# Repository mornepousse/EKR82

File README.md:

# EKR82 Keyboard

Work in Progress...

EN:

I took the Lily58 and added my personal touch by including a column and row layout for ease of use. I added function keys on top for more efficient use of special functions and an extra macro column for even further customization to my liking. And to top it all off, I added a thumb button for easy access to an important function. In short, the EKR82 is a custom keyboard that I created to meet all of my needs

FR:

J'ai pris le Lily58 et j'ai ajouté ma touche personnelle en y incluant une disposition en colonnes et en rangées pour une utilisation facile. J'ai ajouté des touches de fonction en haut pour une utilisation plus efficace des fonctions spéciales et une colonne de macros pour une personnalisation encore plus poussée a mon goût. Et pour couronner le tout, j'ai ajouté une touche pour le pouce pour un accès facile à une fonction importante. Bref, le EKR82 est un clavier sur mesure que j'ai créé pour répondre à tous mes besoins.

lily58 forki

by mornepousse

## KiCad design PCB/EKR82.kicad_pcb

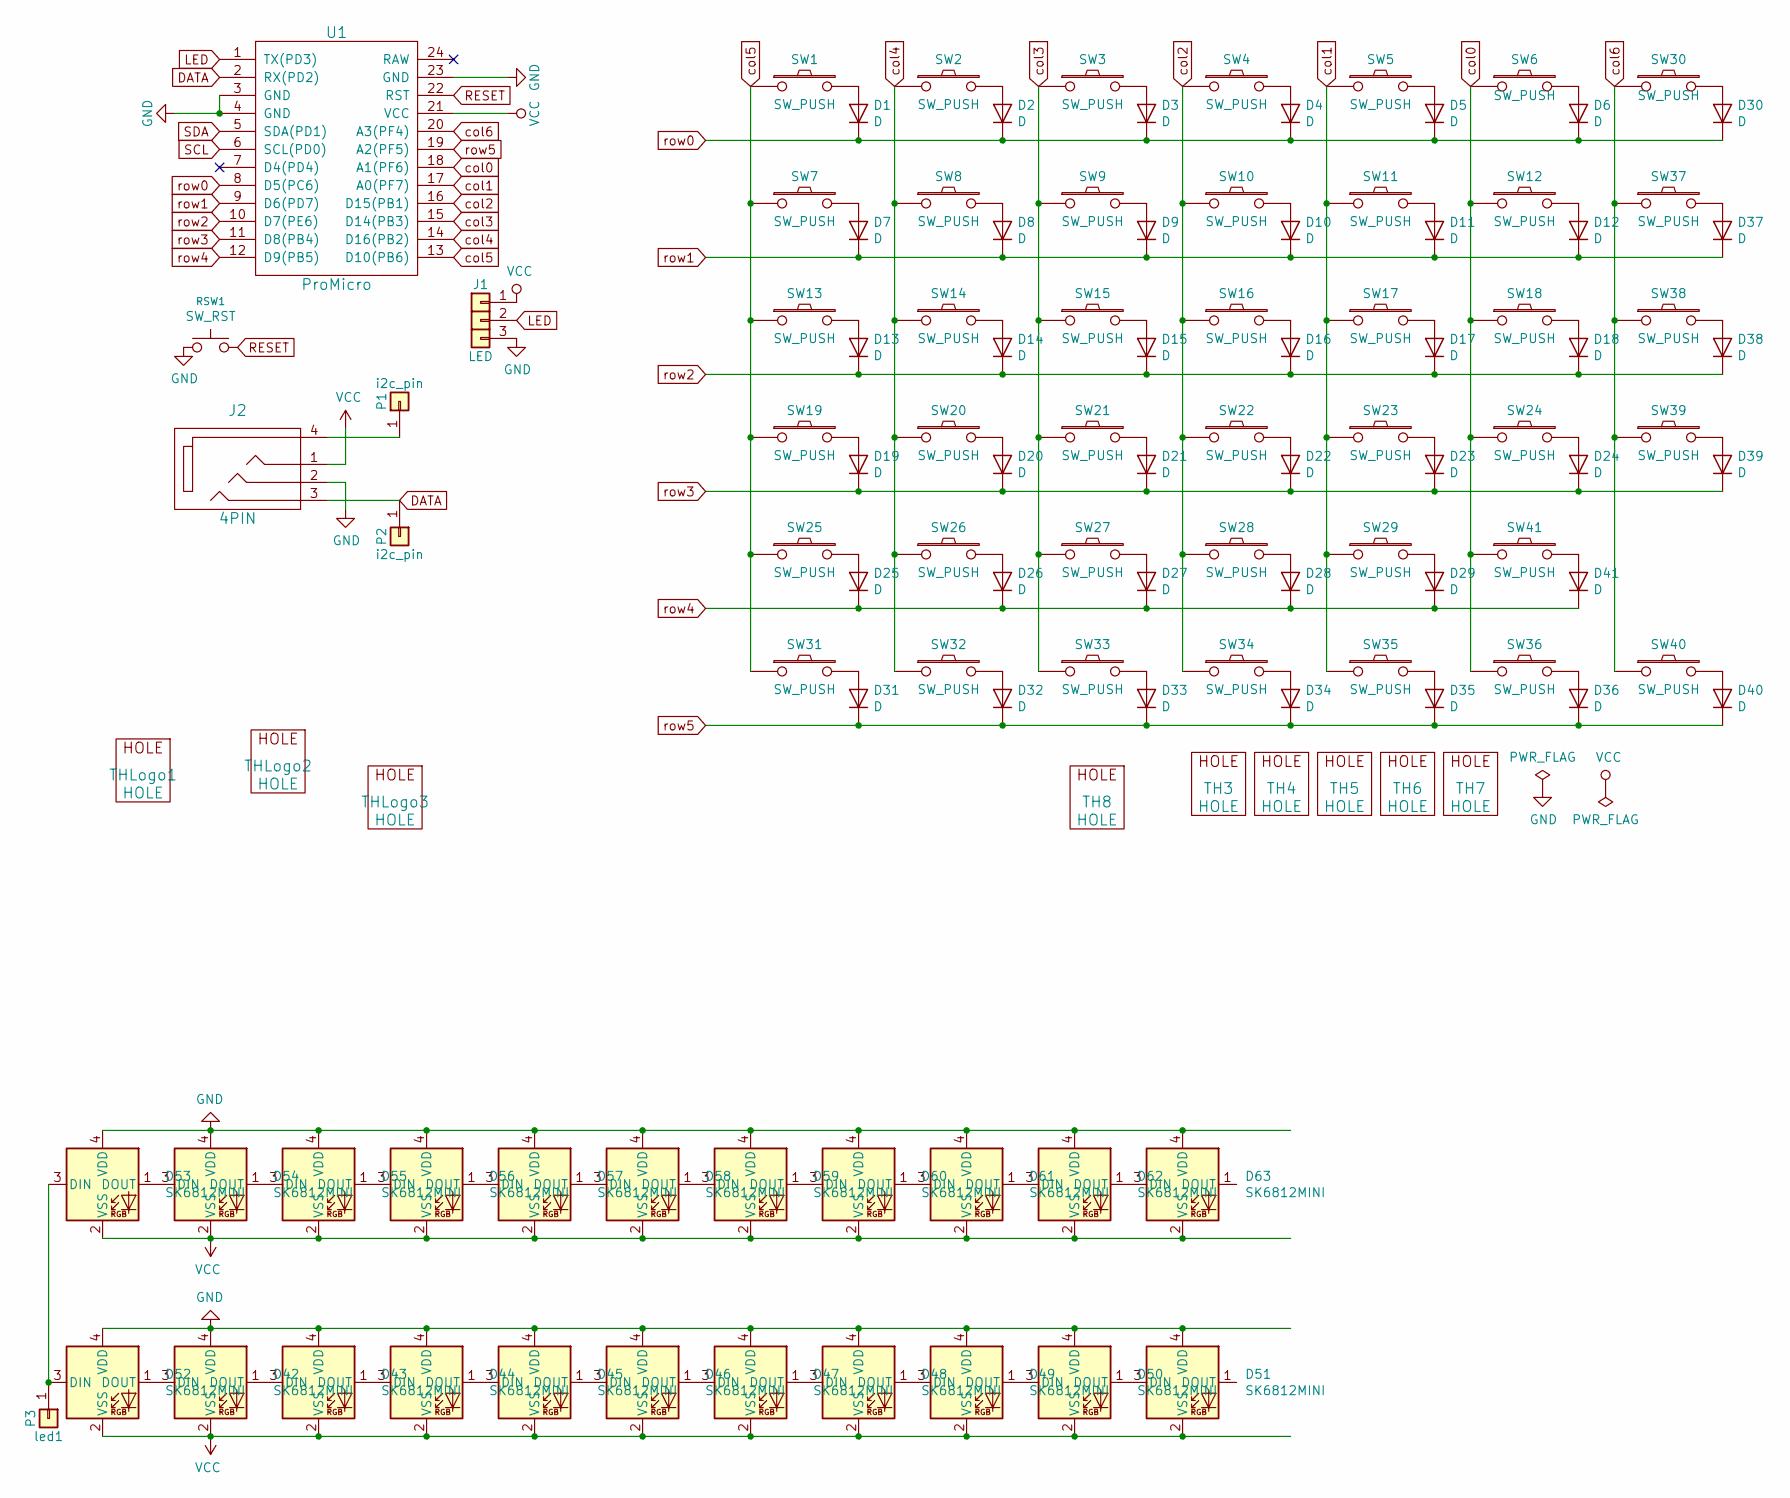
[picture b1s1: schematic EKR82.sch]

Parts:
D1, D2, D3, D4, D5, D6, D7, D8, D9, D10, D11, D12, D13, D14, D15, D16, D17, D18, D19, D20, D21, D22, D23, D24, D25, D26, D27, D28, D29, D30, D31, D32, D33, D34, D35, D36, D37, D38, D39, D40, D41: D; Diode_SOD123
D42, D43, D44, D45, D46, D47, D48, D49, D50, D51, D52, D53, D54, D55, D56, D57, D58, D59, D60, D61, D62, D63: SK6812MINI; LED_SK6812MINI_PLCC4_3.5x3.5mm_P1.75mm
J1: LED
J2: 4PIN; MJ-4PP-9
P1, P2: i2c_pin; 1pin_conn
P3: led1; PinHeader_1x01_P1.27mm_Vertical
RSW1: SW_RST; TACT_SWITCH_TVBP06
SW1, SW2, SW3, SW4, SW5, SW6, SW7, SW8, SW9, SW10, SW11, SW12, SW13, SW14, SW15, SW16, SW17, SW18, SW19, SW20, SW21, SW22, SW23, SW24, SW25, SW26, SW27, SW28, SW29, SW30, SW31, SW32, SW33, SW34, SW35, SW36, SW37, SW38, SW39, SW40, SW41: SW_PUSH; CherryMX_KailhLowProfile_Hotswap_edge-2
TH3, TH4, TH5, TH6, TH7, TH8: HOLE; HOLE_M2_TH
THLogo1: HOLE; EKR82-2
THLogo2, THLogo3: HOLE; OSHW-Symbol_8.9x8mm_SilkScreen
U1: ProMicro; ProMicro_rev

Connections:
DATA: J2.3, P2.1, U1.2 (RX(PD2))
GND: D42.4 (VDD), D43.4 (VDD), D44.4 (VDD), D45.4 (VDD), D46.4 (VDD), D47.4 (VDD), D48.4 (VDD), D49.4 (VDD), D50.4 (VDD), D51.4 (VDD), D52.4 (VDD), D53.4 (VDD), D54.4 (VDD), D55.4 (VDD), D56.4 (VDD), D57.4 (VDD), D58.4 (VDD), D59.4 (VDD), D60.4 (VDD), D61.4 (VDD), D62.4 (VDD), D63.4 (VDD), J1.3, J2.2, RSW1.1, U1.3 (GND), U1.4 (GND), U1.23 (GND)
LED: J1.2, U1.1 (TX(PD3))
unnamed: D1.2 (A), SW1.2
unnamed: D2.2 (A), SW2.2
unnamed: D3.2 (A), SW3.2
unnamed: D4.2 (A), SW4.2
unnamed: D5.2 (A), SW5.2
unnamed: D6.2 (A), SW6.2
unnamed: D7.2 (A), SW7.2
unnamed: D8.2 (A), SW8.2
unnamed: D9.2 (A), SW9.2
unnamed: D10.2 (A), SW10.2
unnamed: D11.2 (A), SW11.2
unnamed: D12.2 (A), SW12.2
unnamed: D13.2 (A), SW13.2
unnamed: D14.2 (A), SW14.2
unnamed: D15.2 (A), SW15.2
unnamed: D16.2 (A), SW16.2
unnamed: D17.2 (A), SW17.2
unnamed: D18.2 (A), SW18.2
unnamed: D19.2 (A), SW19.2
unnamed: D20.2 (A), SW20.2
unnamed: D21.2 (A), SW21.2
unnamed: D22.2 (A), SW22.2
unnamed: D23.2 (A), SW23.2
unnamed: D24.2 (A), SW24.2
unnamed: D25.2 (A), SW25.2
unnamed: D26.2 (A), SW26.2
unnamed: D27.2 (A), SW27.2
unnamed: D28.2 (A), SW28.2
unnamed: D29.2 (A), SW29.2
unnamed: D30.2 (A), SW30.2
unnamed: D31.2 (A), SW31.2
unnamed: D32.2 (A), SW32.2
unnamed: D33.2 (A), SW33.2
unnamed: D34.2 (A), SW34.2
unnamed: D35.2 (A), SW35.2
unnamed: D36.2 (A), SW36.2
unnamed: D37.2 (A), SW37.2
unnamed: D38.2 (A), SW38.2
unnamed: D39.2 (A), SW39.2
unnamed: D40.2 (A), SW40.2
unnamed: D41.2 (A), SW41.2
unnamed: D42.1 (DOUT), D43.3 (DIN)
unnamed: D42.3 (DIN), D52.1 (DOUT)
unnamed: D43.1 (DOUT), D44.3 (DIN)
unnamed: D44.1 (DOUT), D45.3 (DIN)
unnamed: D45.1 (DOUT), D46.3 (DIN)
unnamed: D46.1 (DOUT), D47.3 (DIN)
unnamed: D47.1 (DOUT), D48.3 (DIN)
unnamed: D48.1 (DOUT), D49.3 (DIN)
unnamed: D49.1 (DOUT), D50.3 (DIN)
unnamed: D50.1 (DOUT), D51.3 (DIN)
unnamed 55: D52.3 (DIN), D53.3 (DIN), P3.1; also elsewhere on the board
unnamed: D53.1 (DOUT), D54.3 (DIN)
unnamed: D54.1 (DOUT), D55.3 (DIN)
unnamed: D55.1 (DOUT), D56.3 (DIN)
unnamed: D56.1 (DOUT), D57.3 (DIN)
unnamed: D57.1 (DOUT), D58.3 (DIN)
unnamed: D58.1 (DOUT), D59.3 (DIN)
unnamed: D59.1 (DOUT), D60.3 (DIN)
unnamed: D60.1 (DOUT), D61.3 (DIN)
unnamed: D61.1 (DOUT), D62.3 (DIN)
unnamed: D62.1 (DOUT), D63.3 (DIN)
unnamed: J2.4, P1.1
RESET: RSW1.2, U1.22 (RST)
SCL: U1.6 (SCL(PD0))
SDA: U1.5 (SDA(PD1))
VCC: D42.2 (VSS), D43.2 (VSS), D44.2 (VSS), D45.2 (VSS), D46.2 (VSS), D47.2 (VSS), D48.2 (VSS), D49.2 (VSS), D50.2 (VSS), D51.2 (VSS), D52.2 (VSS), D53.2 (VSS), D54.2 (VSS), D55.2 (VSS), D56.2 (VSS), D57.2 (VSS), D58.2 (VSS), D59.2 (VSS), D60.2 (VSS), D61.2 (VSS), D62.2 (VSS), D63.2 (VSS), J1.1, J2.1, U1.21 (VCC)
col0: SW6.1, SW12.1, SW18.1, SW24.1, SW36.1, SW41.1, U1.18 (A1(PF6))
col1: SW5.1, SW11.1, SW17.1, SW23.1, SW29.1, SW35.1, U1.17 (A0(PF7))
col2: SW4.1, SW10.1, SW16.1, SW22.1, SW28.1, SW34.1, U1.16 (D15(PB1))
col3: SW3.1, SW9.1, SW15.1, SW21.1, SW27.1, SW33.1, U1.15 (D14(PB3))
col4: SW2.1, SW8.1, SW14.1, SW20.1, SW26.1, SW32.1, U1.14 (D16(PB2))
col5: SW1.1, SW7.1, SW13.1, SW19.1, SW25.1, SW31.1, U1.13 (D10(PB6))
col6: SW30.1, SW37.1, SW38.1, SW39.1, SW40.1, U1.20 (A3(PF4))
row0: D1.1 (K), D2.1 (K), D3.1 (K), D4.1 (K), D5.1 (K), D6.1 (K), D30.1 (K), U1.8 (D5(PC6))
row1: D7.1 (K), D8.1 (K), D9.1 (K), D10.1 (K), D11.1 (K), D12.1 (K), D37.1 (K), U1.9 (D6(PD7))
row2: D13.1 (K), D14.1 (K), D15.1 (K), D16.1 (K), D17.1 (K), D18.1 (K), D38.1 (K), U1.10 (D7(PE6))
row3: D19.1 (K), D20.1 (K), D21.1 (K), D22.1 (K), D23.1 (K), D24.1 (K), D39.1 (K), U1.11 (D8(PB4))
row4: D25.1 (K), D26.1 (K), D27.1 (K), D28.1 (K), D29.1 (K), D41.1 (K), U1.12 (D9(PB5))
row5: D31.1 (K), D32.1 (K), D33.1 (K), D34.1 (K), D35.1 (K), D36.1 (K), D40.1 (K), U1.19 (A2(PF5))

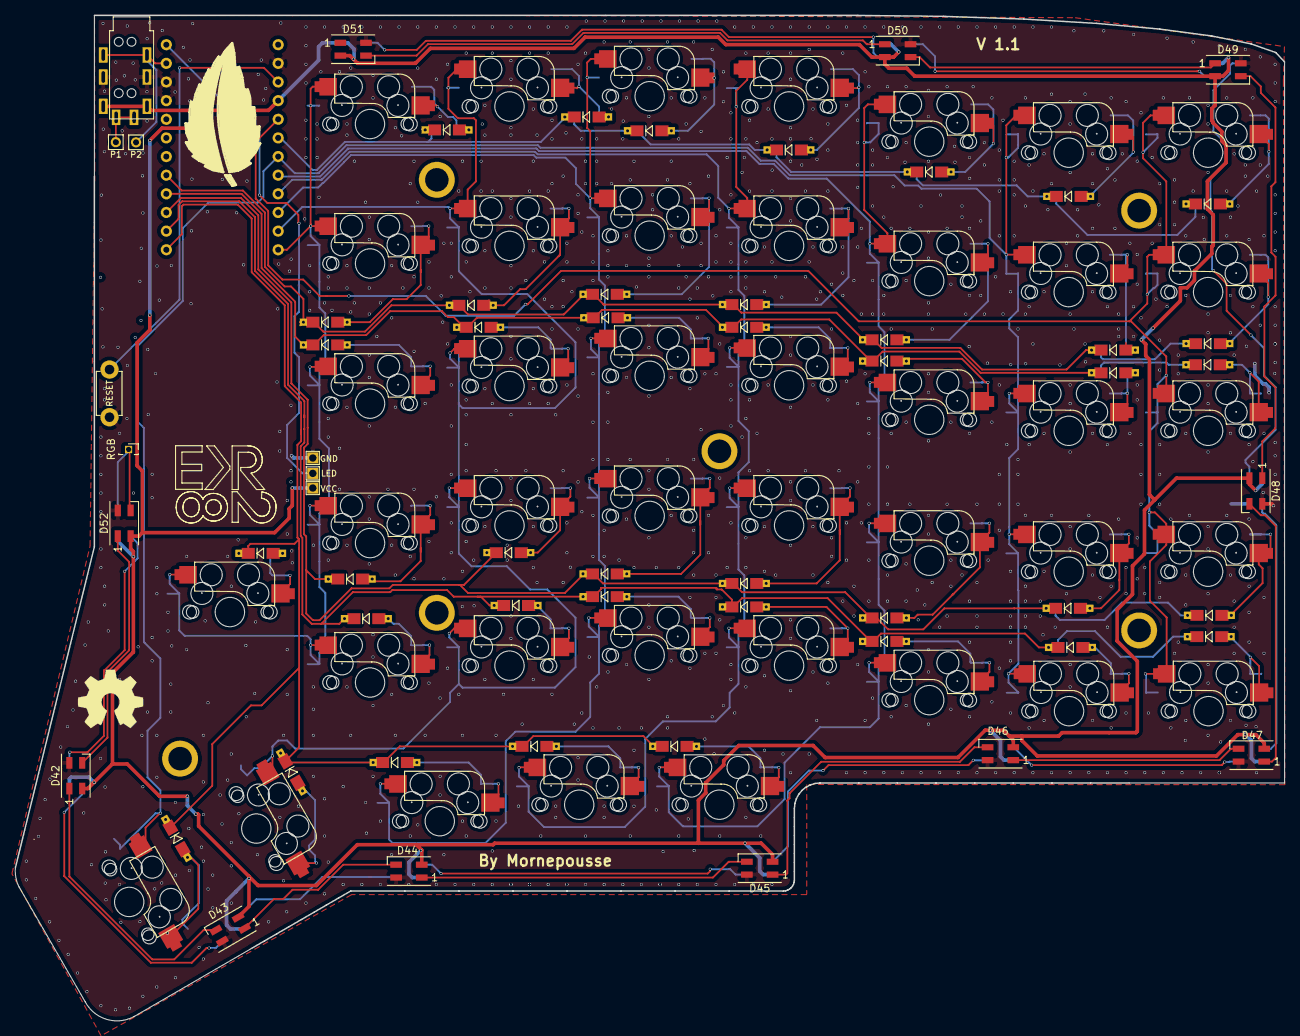
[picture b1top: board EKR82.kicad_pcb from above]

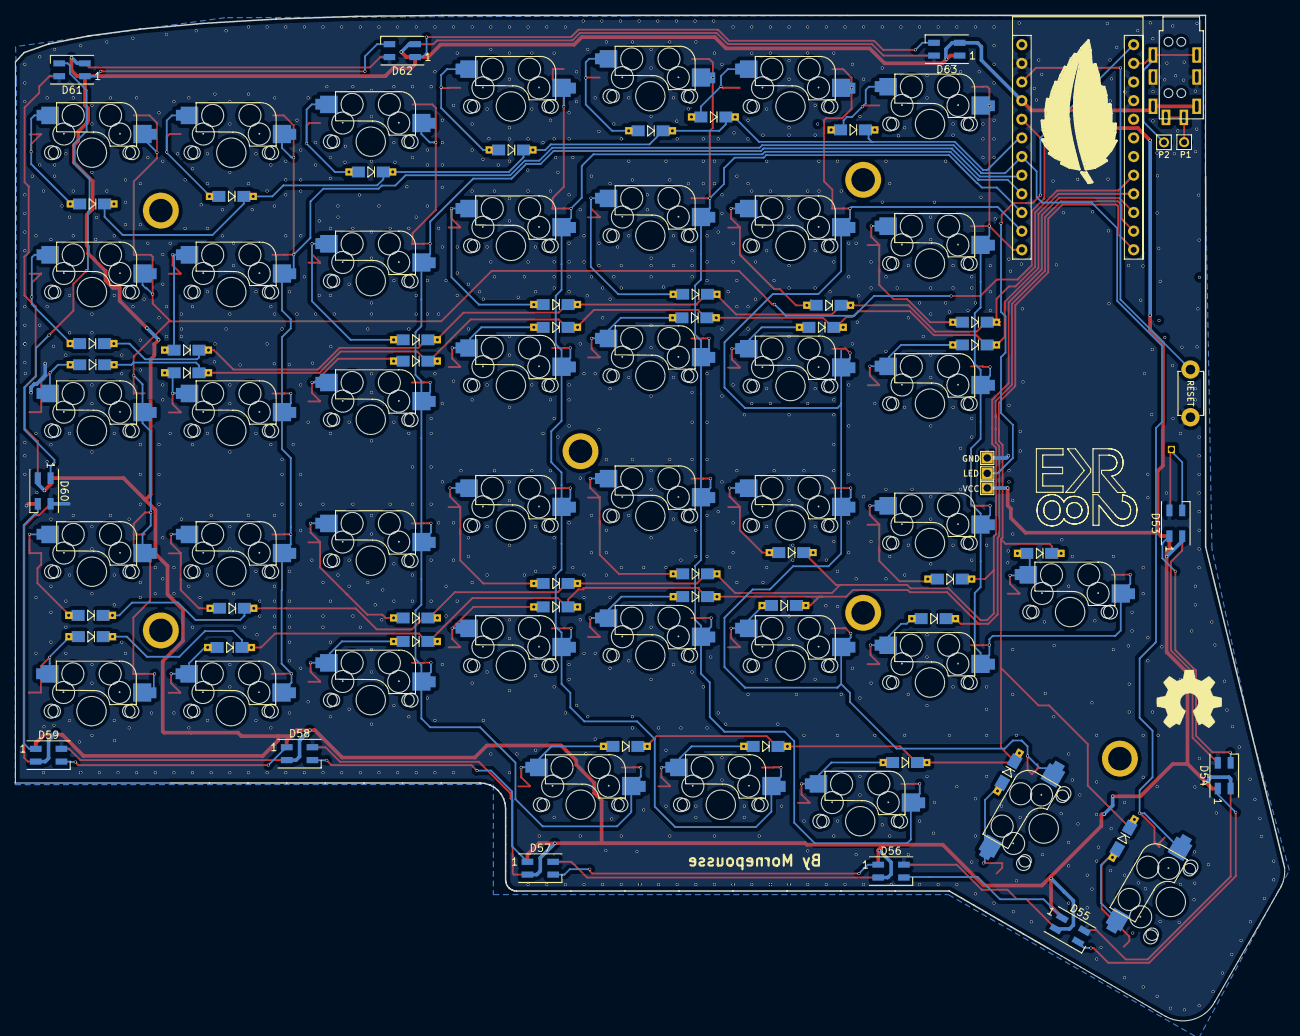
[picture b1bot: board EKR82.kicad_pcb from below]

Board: 2 copper layers, 173.0 x 137.0 mm, 121 parts (13 on the bottom side), 81 nets.

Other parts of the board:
RGB: led1; PinSocket_1x01_P1.27mm_Vertical
THLogo1#2: HOLE; EKR82-2

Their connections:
unnamed 55: RGB.1; also elsewhere on the board

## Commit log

2021-05-26 rm .vs
2021-05-26 update kicad project
2021-05-26 SLEEP_LED_ENABLE = no
2021-05-26 BOOTLOADER = bootloadHID
2021-05-26 aoeu
2021-05-26 change name lily58 to EKR82
2021-05-26 rename kicad project EKR82_Pro to EKR82
2021-05-26 edit readme
2021-05-26 test merge
2021-05-26 Work in Progress...
2021-05-26 test via vs code
2021-05-26 forko
2021-05-26 forki
2021-05-26 conflic test 3
2021-05-27 add json for VIA
2021-05-27 QMK firmware part work update
2021-05-27 edit readme un qmk part
2021-06-08 move SW41 and remove resistors
2021-06-09 add backlight rgb WIP
2021-06-09 add led and logo
2021-06-09 add image jlc
2021-06-16 Add top PCB and change diode footprint
2021-06-17 change arduino footprint and move
2021-06-17 Set theme jekyll-theme-slate
2021-06-18 little ajustements
2021-07-15 Add PCB 3D image
2021-08-03 Set theme jekyll-theme-cayman
2023-02-12 Add Keyboard image
